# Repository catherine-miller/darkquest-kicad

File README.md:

# darkquest-kicad
KiCad projects for the DarkQuest EMCal readout
Each folder contains a KiCad project called <title>.kicad_pro
The revision number is in the title of each folder.

As of June 2024, the revisions in use are

SiPM motherboard with attenuator: 6.1

SiPM motherboard, no attenuator: 6.2 (use a 0 ohm resistor on resistor pad or a solder blob)

Chip carrier Rev 2.0

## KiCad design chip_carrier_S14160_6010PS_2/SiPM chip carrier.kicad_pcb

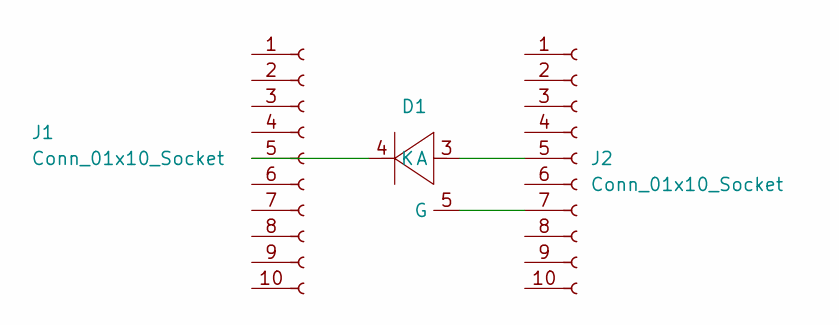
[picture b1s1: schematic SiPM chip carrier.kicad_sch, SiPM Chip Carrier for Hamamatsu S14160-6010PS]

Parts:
D1: S14160_6010PS
J1, J2: Conn_01x10_Socket; PinHeader_1x10_P2.54mm_Vertical

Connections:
unnamed: D1.3 (A), J2.5
unnamed: D1.5 (G), J2.7
unnamed: D1.4 (K), J1.5

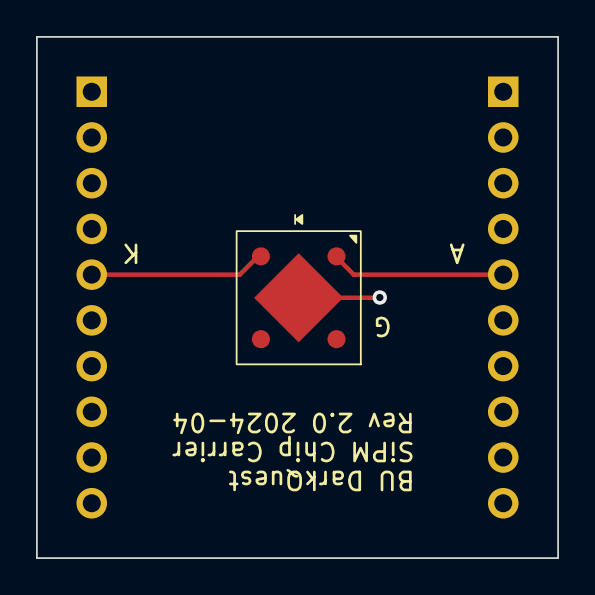
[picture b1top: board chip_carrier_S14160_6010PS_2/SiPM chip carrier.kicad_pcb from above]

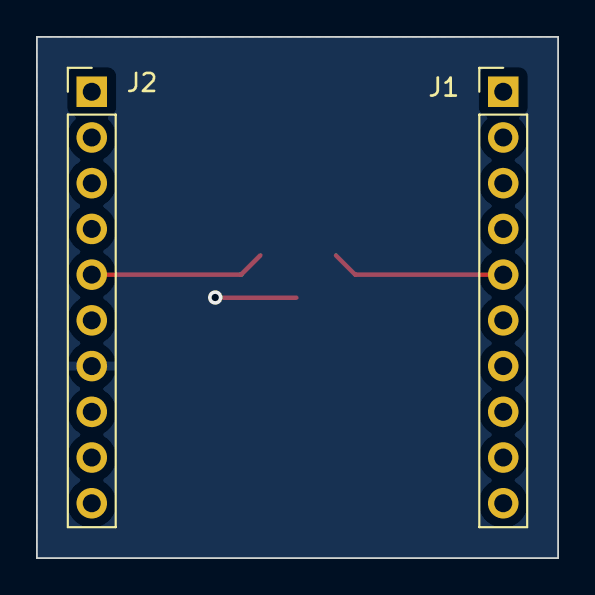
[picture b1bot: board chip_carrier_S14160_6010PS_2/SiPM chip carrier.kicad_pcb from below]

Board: 2 copper layers, 29.0 x 29.0 mm, 3 parts (2 on the bottom side), 3 nets.

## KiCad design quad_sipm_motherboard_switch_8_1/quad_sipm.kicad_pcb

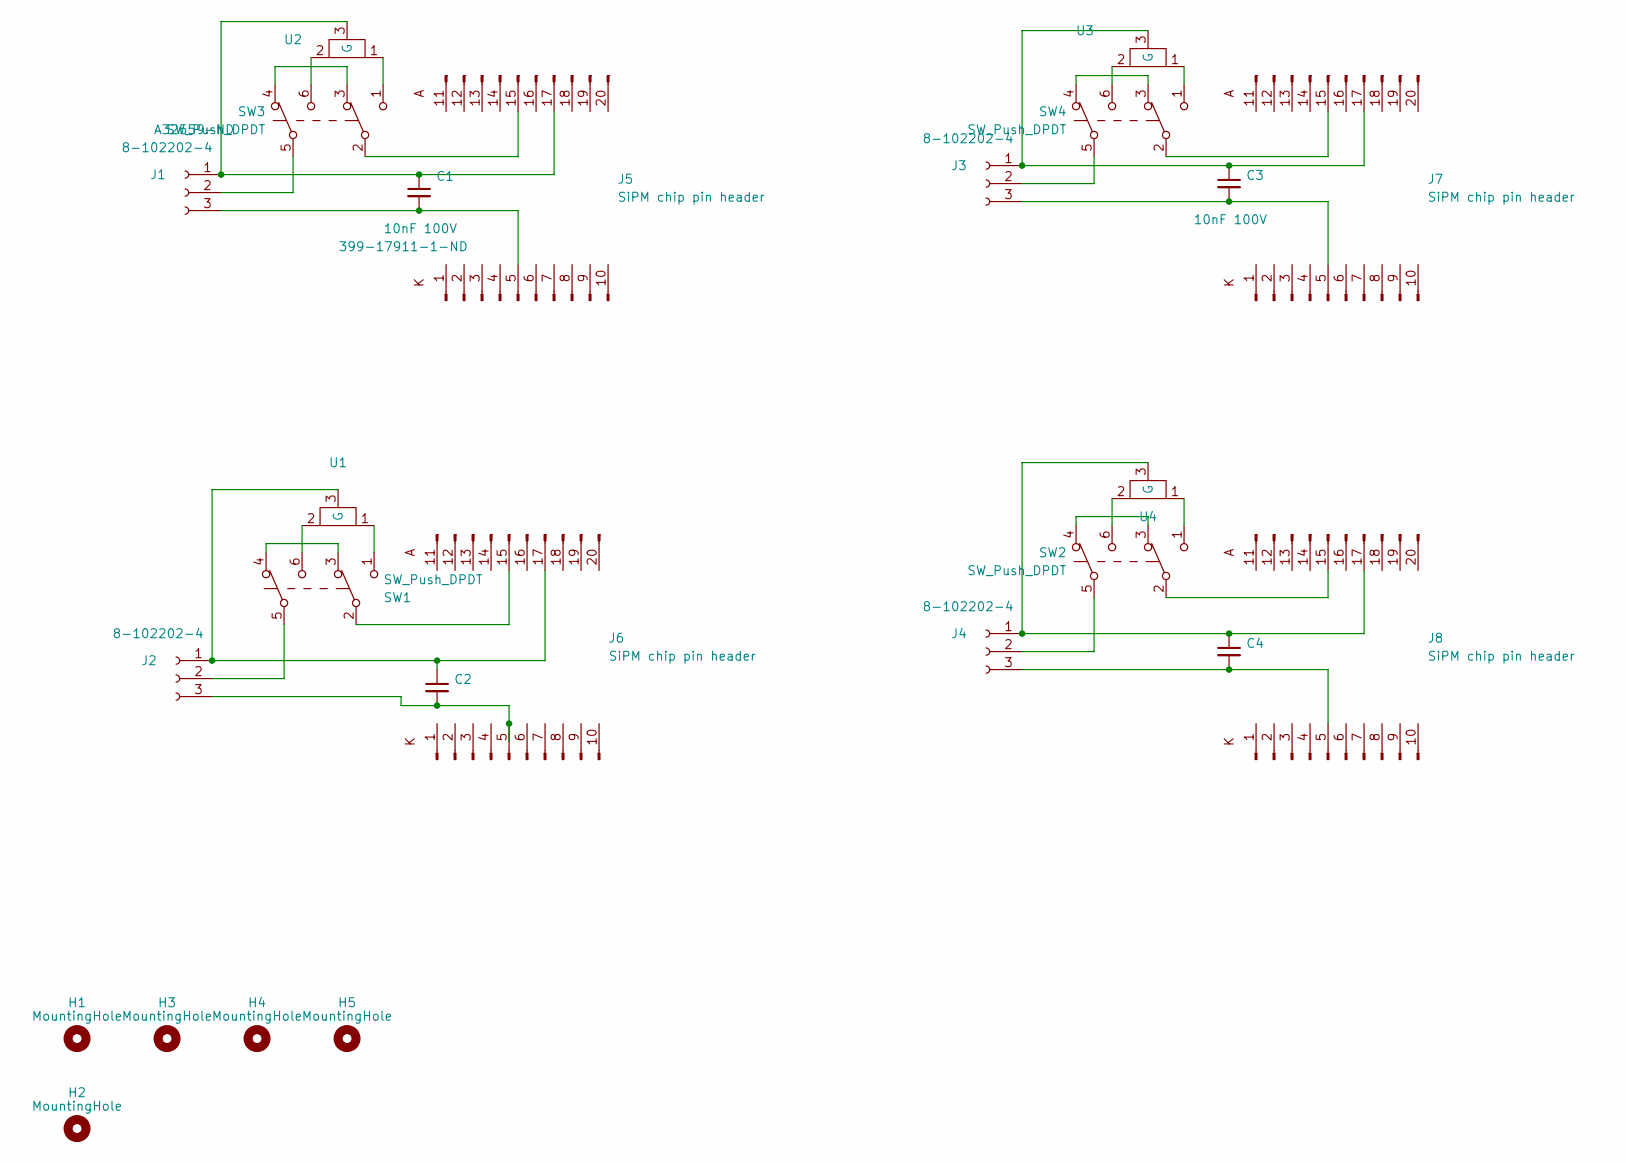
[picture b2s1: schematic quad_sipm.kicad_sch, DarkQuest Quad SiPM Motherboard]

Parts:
C1, C2, C3, C4: 10nF 100V; C_1206_3216Metric_Pad1.33x1.80mm_HandSolder; DigiKey 399-17911-1-ND
H1, H3, H4, H5: MountingHole; MountingHole_6.4_pad
H2: MountingHole; MountingHole_8.4mm_M8_Pad
J1, J2, J3, J4: 8-102202-4; PinHeader_1x03_P2.54mm_Vertical; DigiKey A32559-ND
J5, J6, J7, J8: SiPM chip pin header; chip_carrier_pin_header
SW1, SW2, SW3, SW4: SW_Push_DPDT; Nidec_DPDT_CS422YTA
U1, U2, U3, U4: D10AA20Z4

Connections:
unnamed: C1.1, J1.1, J5.17 (Pin_7), U2.3 (G)
unnamed: J1.2, SW3.5 (B)
unnamed: C1.2, J1.3, J5.5
unnamed: C2.1, J2.1, J6.17 (Pin_7), U1.3 (G)
unnamed: J2.2, SW1.5 (B)
unnamed: C2.2, J2.3, J6.5
unnamed: C3.1, J3.1, J7.17 (Pin_7), U3.3 (G)
unnamed: J3.2, SW4.5 (B)
unnamed: C3.2, J3.3, J7.5
unnamed: C4.1, J4.1, J8.17 (Pin_7), U4.3 (G)
unnamed: J4.2, SW2.5 (B)
unnamed: C4.2, J4.3, J8.5
unnamed: J5.15 (Pin_5), SW3.2
unnamed: J6.15 (Pin_5), SW1.2
unnamed: J7.15 (Pin_5), SW4.2
unnamed: J8.15 (Pin_5), SW2.2
unnamed: SW1.6 (0), U1.2
unnamed: SW1.3 (A), SW1.4 (A)
unnamed: SW1.1 (C), U1.1
unnamed: SW2.6 (0), U4.2
unnamed: SW2.3 (A), SW2.4 (A)
unnamed: SW2.1 (C), U4.1
unnamed: SW3.6 (0), U2.2
unnamed: SW3.3 (A), SW3.4 (A)
unnamed: SW3.1 (C), U2.1
unnamed: SW4.6 (0), U3.2
unnamed: SW4.3 (A), SW4.4 (A)
unnamed: SW4.1 (C), U3.1

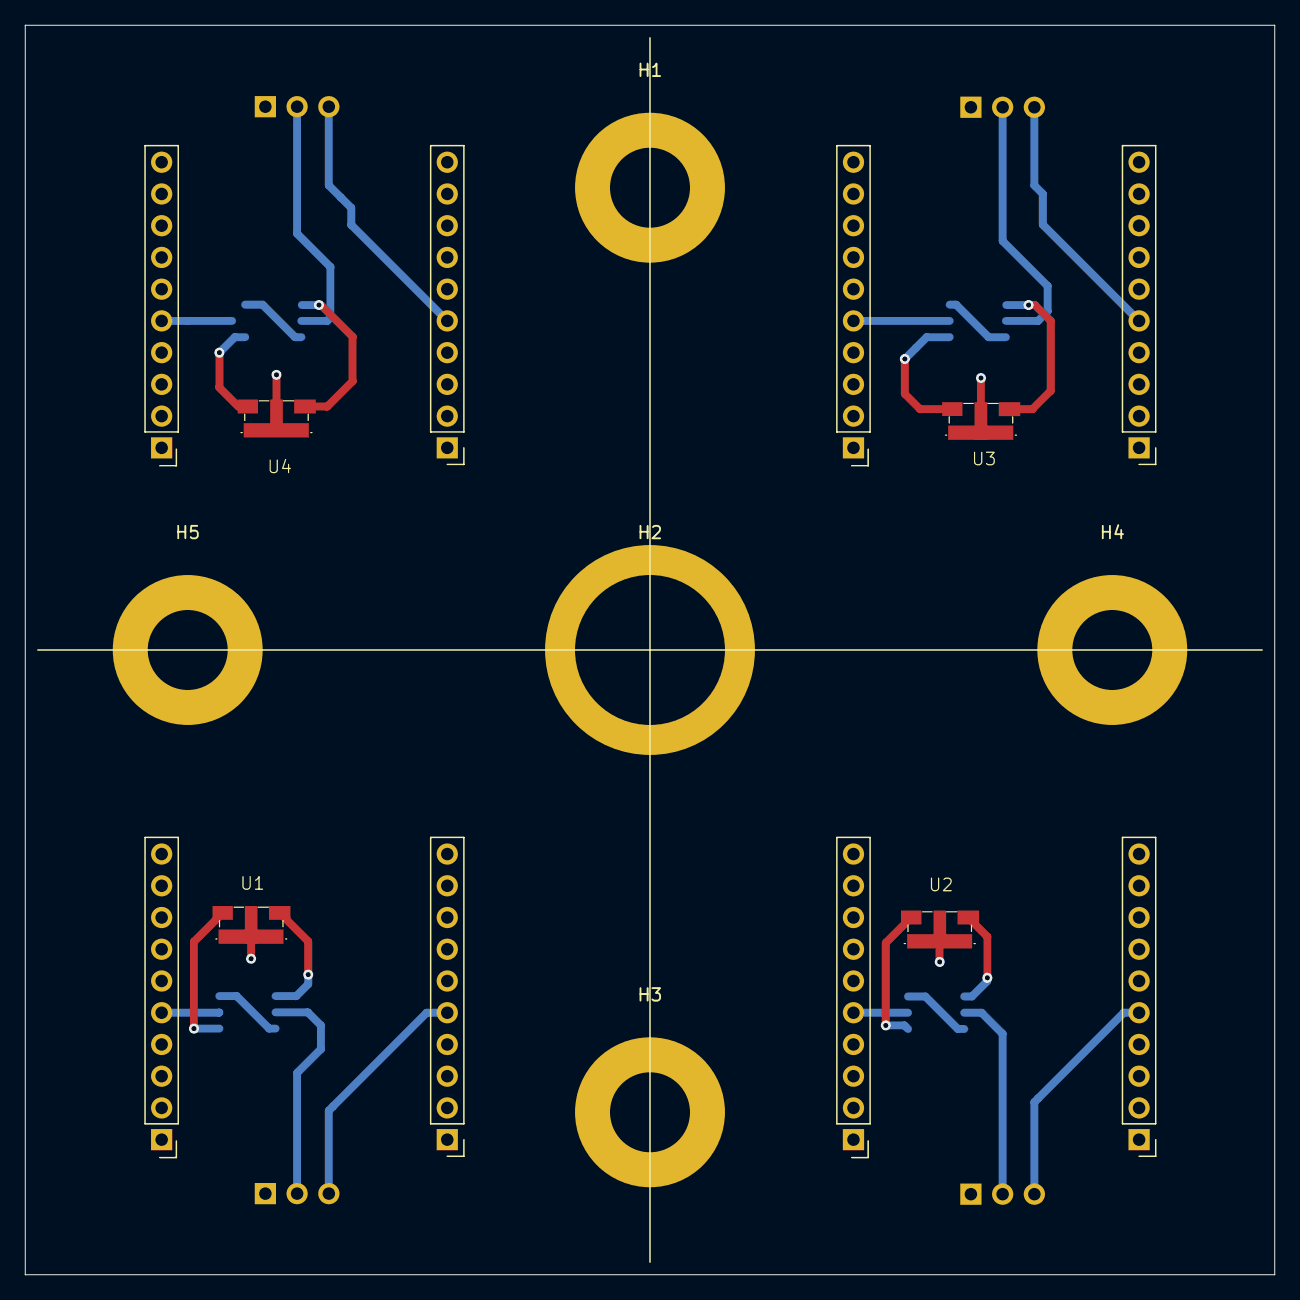
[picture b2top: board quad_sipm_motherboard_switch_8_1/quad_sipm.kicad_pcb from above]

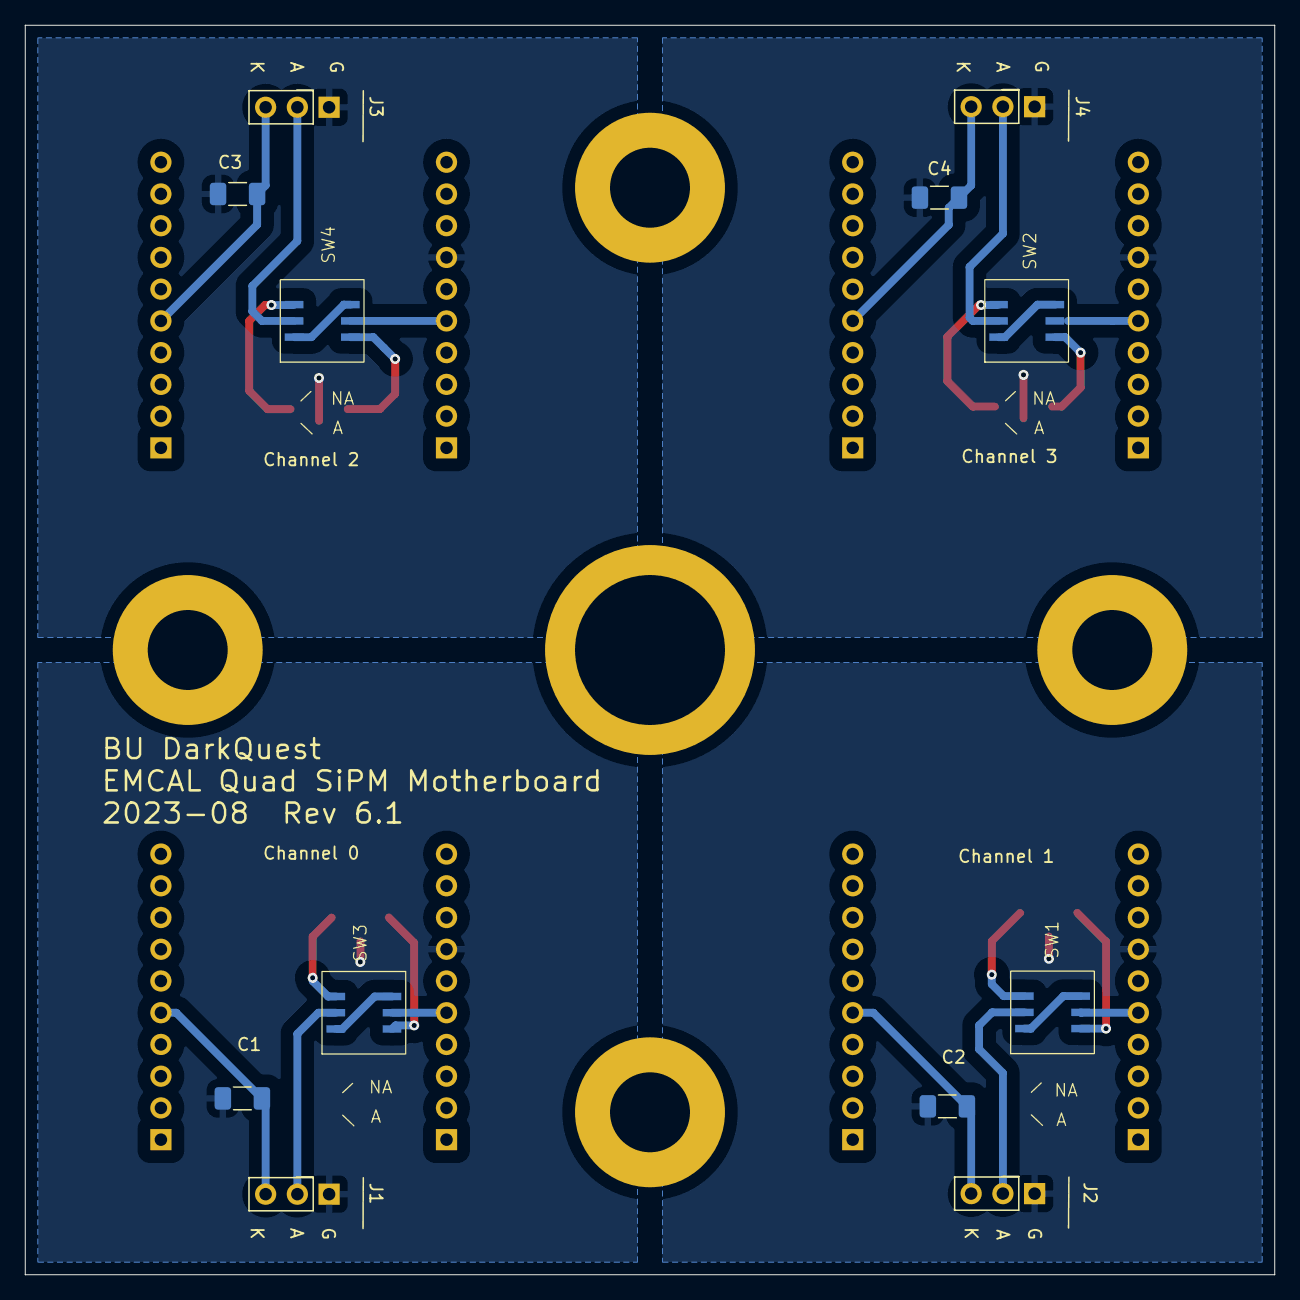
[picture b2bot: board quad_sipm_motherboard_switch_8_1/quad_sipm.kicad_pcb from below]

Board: 2 copper layers, 100.0 x 100.0 mm, 25 parts (12 on the bottom side), 28 nets.

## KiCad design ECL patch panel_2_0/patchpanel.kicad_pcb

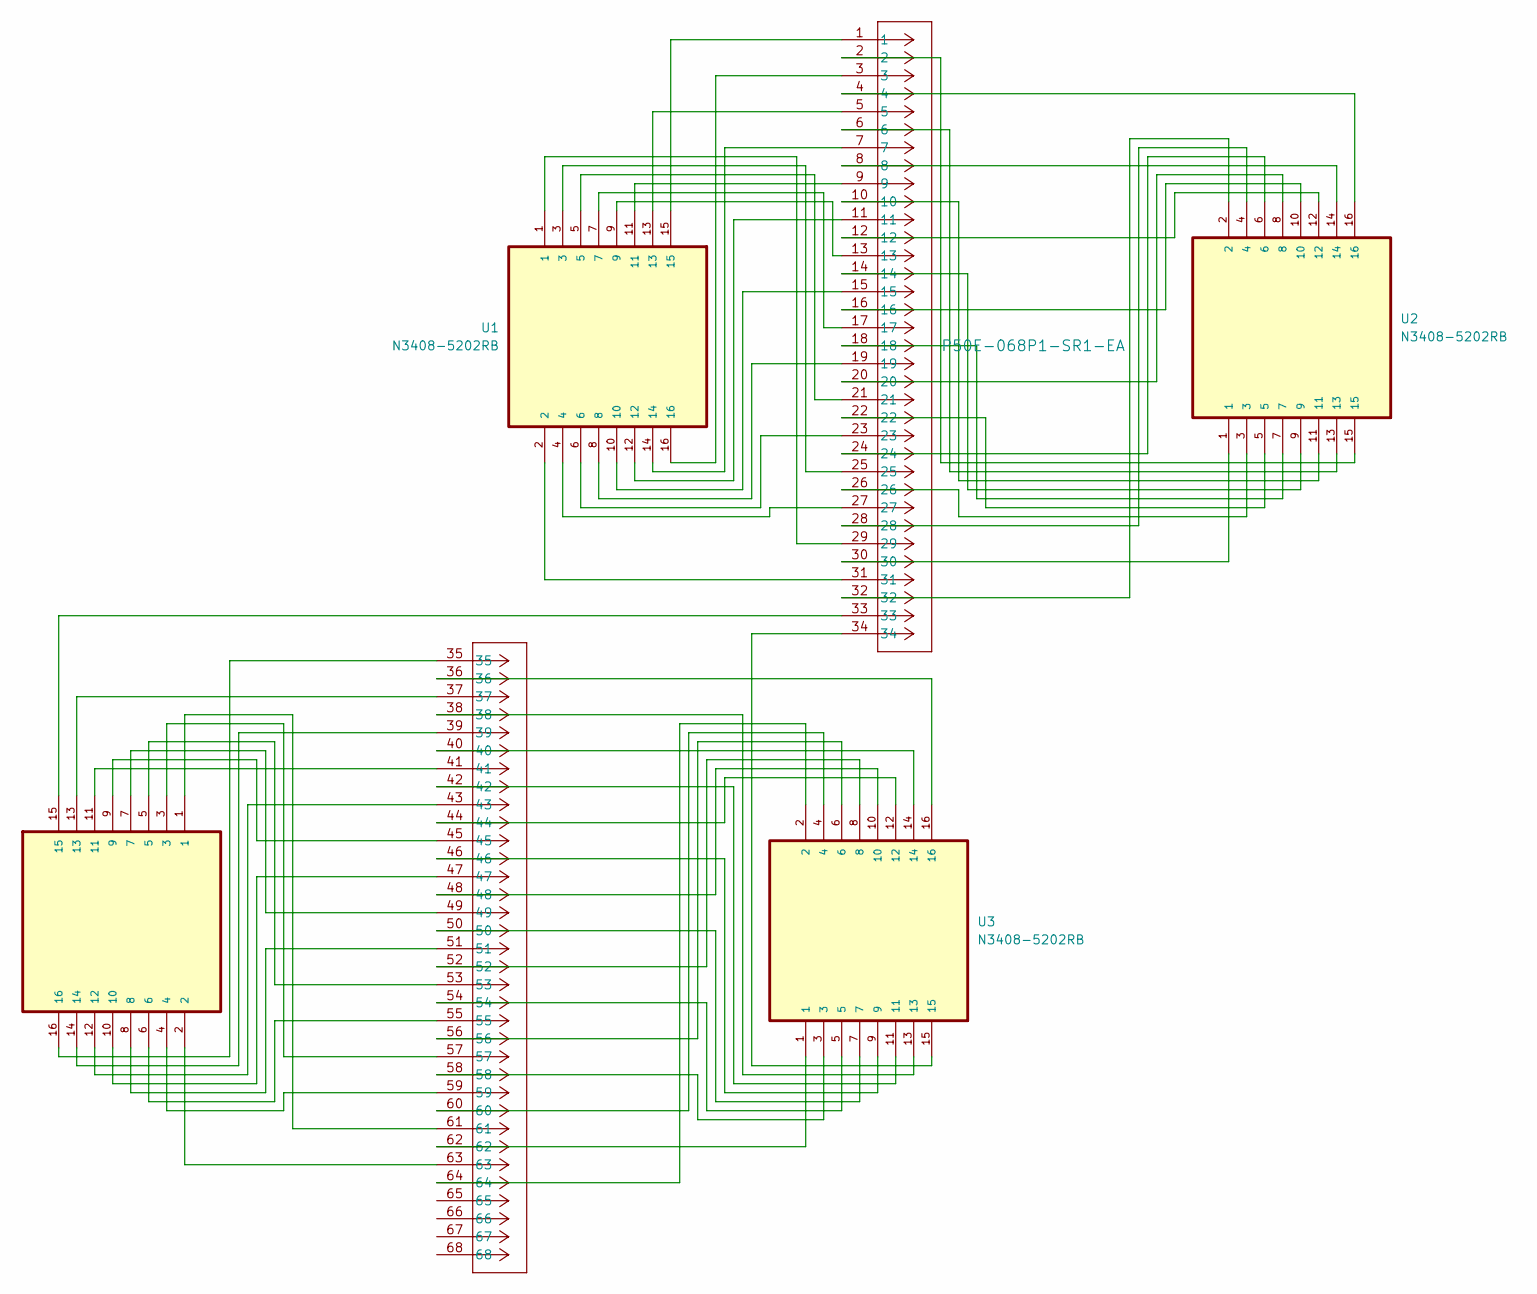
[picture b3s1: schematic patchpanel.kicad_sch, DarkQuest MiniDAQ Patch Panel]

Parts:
J1: P50E-068P1-SR1-EA; CONN_P50E-068P1-SR1-EA_3MM
U1, U2, U3, U4: N3408-5202RB; 3M_N3408-5202RB; MPN N3408-5202RB

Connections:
unnamed: J1.1, U1.15
unnamed: J1.2, U2.15
unnamed: J1.3, U1.16
unnamed: J1.4, U2.16
unnamed: J1.5, U1.13
unnamed: J1.6, U2.13
unnamed: J1.7, U1.14
unnamed: J1.8, U2.14
unnamed: J1.9, U1.11
unnamed: J1.10, U2.11
unnamed: J1.11, U1.12
unnamed: J1.12, U2.12
unnamed: J1.13, U1.9
unnamed: J1.14, U2.9
unnamed: J1.15, U1.10
unnamed: J1.16, U2.10
unnamed: J1.17, U1.7
unnamed: J1.18, U2.7
unnamed: J1.19, U1.8
unnamed: J1.20, U2.8
unnamed: J1.21, U1.5
unnamed: J1.22, U2.5
unnamed: J1.23, U1.6
unnamed: J1.24, U2.6
unnamed: J1.25, U1.3
unnamed: J1.26, U2.3
unnamed: J1.27, U1.4
unnamed: J1.28, U2.4
unnamed: J1.29, U1.1
unnamed: J1.30, U2.1
unnamed: J1.31, U1.2
unnamed: J1.32, U2.2
unnamed: J1.33, U4.15
unnamed: J1.34, U3.15
unnamed: J1.35, U4.16
unnamed: J1.36, U3.16
unnamed: J1.37, U4.13
unnamed: J1.38, U3.13
unnamed: J1.39, U4.14
unnamed: J1.40, U3.14
unnamed: J1.41, U4.11
unnamed: J1.42, U3.11
unnamed: J1.43, U4.12
unnamed: J1.44, U3.12
unnamed: J1.45, U4.9
unnamed: J1.46, U3.9
unnamed: J1.47, U4.10
unnamed: J1.48, U3.10
unnamed: J1.49, U4.7
unnamed: J1.50, U3.7
unnamed: J1.51, U4.8
unnamed: J1.52, U3.8
unnamed: J1.53, U4.5
unnamed: J1.54, U3.5
unnamed: J1.55, U4.6
unnamed: J1.56, U3.6
unnamed: J1.57, U4.3
unnamed: J1.58, U3.3
unnamed: J1.59, U4.4
unnamed: J1.60, U3.4
unnamed: J1.61, U4.1
unnamed: J1.62, U3.1
unnamed: J1.63, U4.2
unnamed: J1.64, U3.2

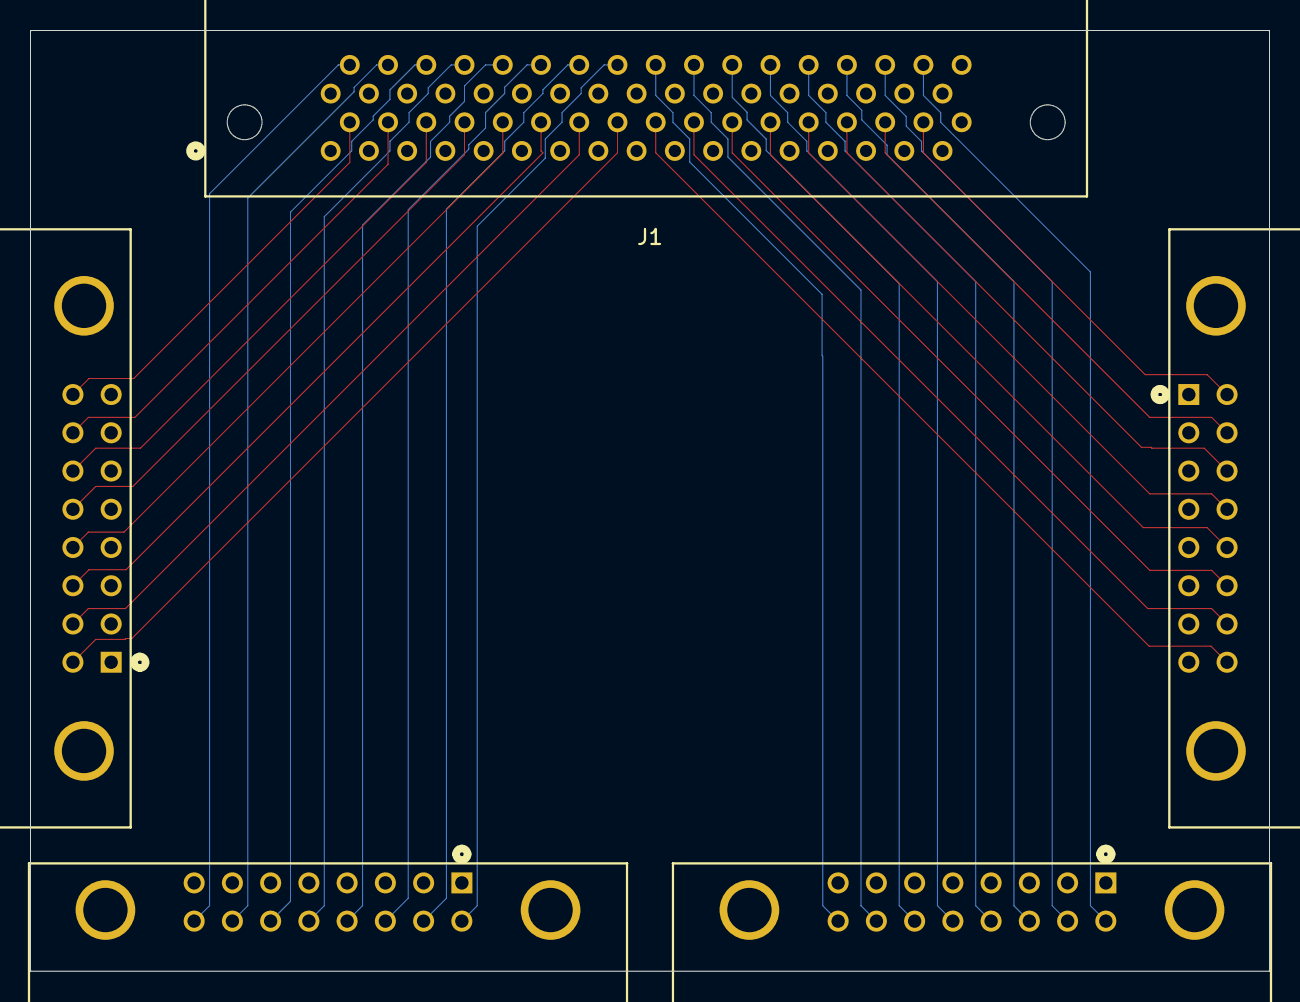
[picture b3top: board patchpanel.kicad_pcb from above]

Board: 4 copper layers, 82.3 x 62.5 mm, 5 parts (0 on the bottom side), 64 nets.

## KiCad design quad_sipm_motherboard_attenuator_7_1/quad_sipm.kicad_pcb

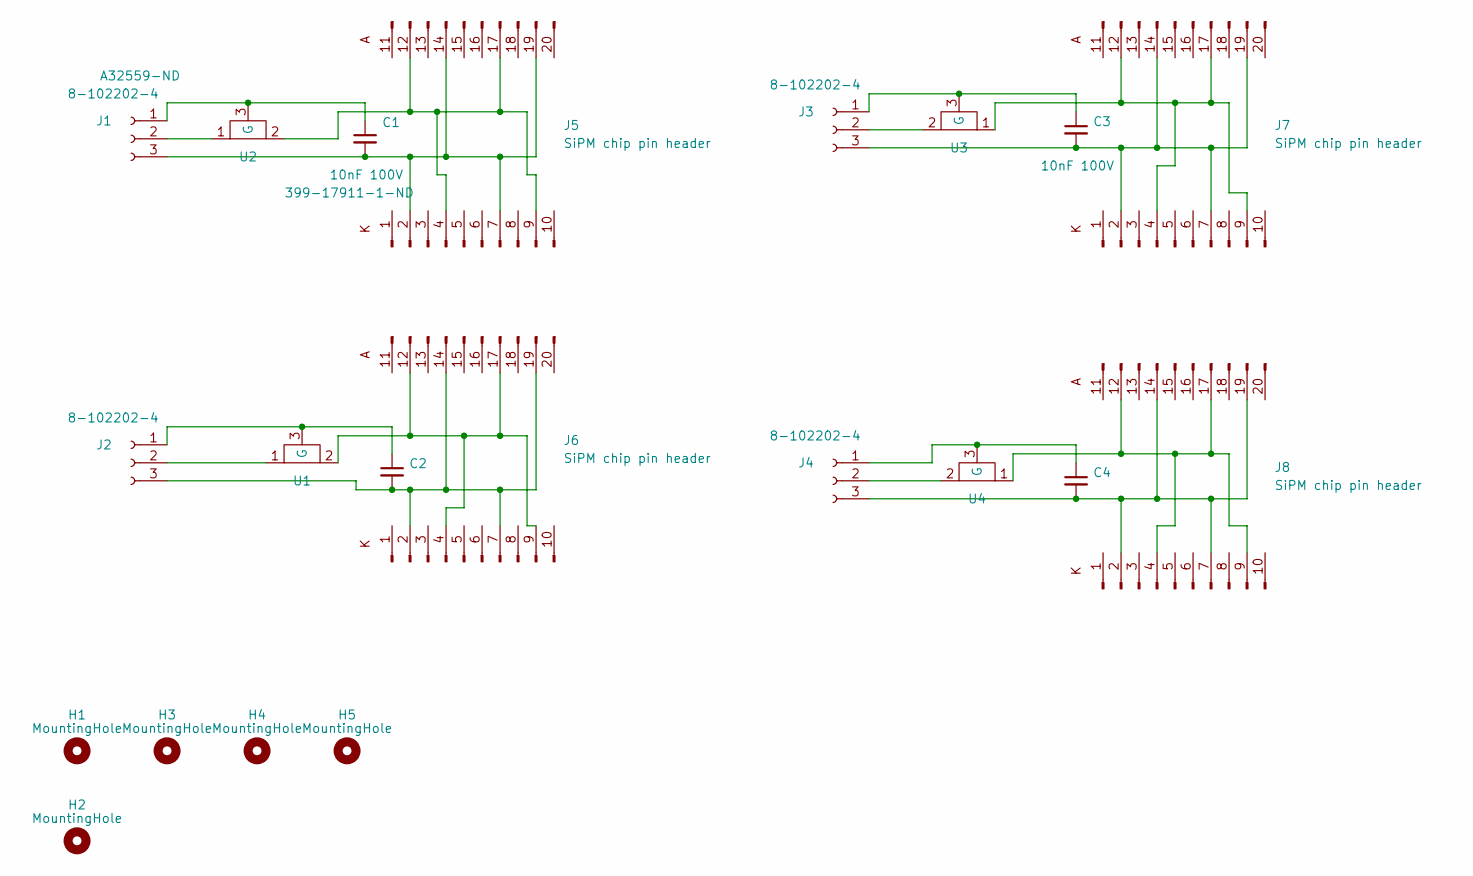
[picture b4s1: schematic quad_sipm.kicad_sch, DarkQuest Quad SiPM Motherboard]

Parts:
C1, C2, C3, C4: 10nF 100V; C_1206_3216Metric_Pad1.33x1.80mm_HandSolder; DigiKey 399-17911-1-ND
H1, H3, H4, H5: MountingHole; MountingHole_6.4_pad
H2: MountingHole; MountingHole_8.4mm_M8_Pad
J1, J2, J3, J4: 8-102202-4; PinHeader_1x03_P2.54mm_Vertical; DigiKey A32559-ND
J5, J6, J7, J8: SiPM chip pin header; chip_carrier_pin_header
U1, U2, U3, U4: D10AA20Z4

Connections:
unnamed: C1.1, J1.1, U2.3 (G)
unnamed: J1.2, U2.1
unnamed: C1.2, J1.3, J5.2, J5.7, J5.14 (Pin_4), J5.19 (Pin_9)
unnamed: C2.1, J2.1, U1.3 (G)
unnamed: J2.2, U1.1
unnamed: C2.2, J2.3, J6.2, J6.7, J6.14 (Pin_4), J6.19 (Pin_9)
unnamed: C3.1, J3.1, U3.3 (G)
unnamed: J3.2, U3.2
unnamed: C3.2, J3.3, J7.2, J7.7, J7.14 (Pin_4), J7.19 (Pin_9)
unnamed: C4.1, J4.1, U4.3 (G)
unnamed: J4.2, U4.2
unnamed: C4.2, J4.3, J8.2, J8.7, J8.14 (Pin_4), J8.19 (Pin_9)
unnamed: J5.4, J5.9, J5.12 (Pin_2), J5.17 (Pin_7), U2.2
unnamed: J6.4, J6.9, J6.12 (Pin_2), J6.17 (Pin_7), U1.2
unnamed: J7.4, J7.9, J7.12 (Pin_2), J7.17 (Pin_7), U3.1
unnamed: J8.4, J8.9, J8.12 (Pin_2), J8.17 (Pin_7), U4.1

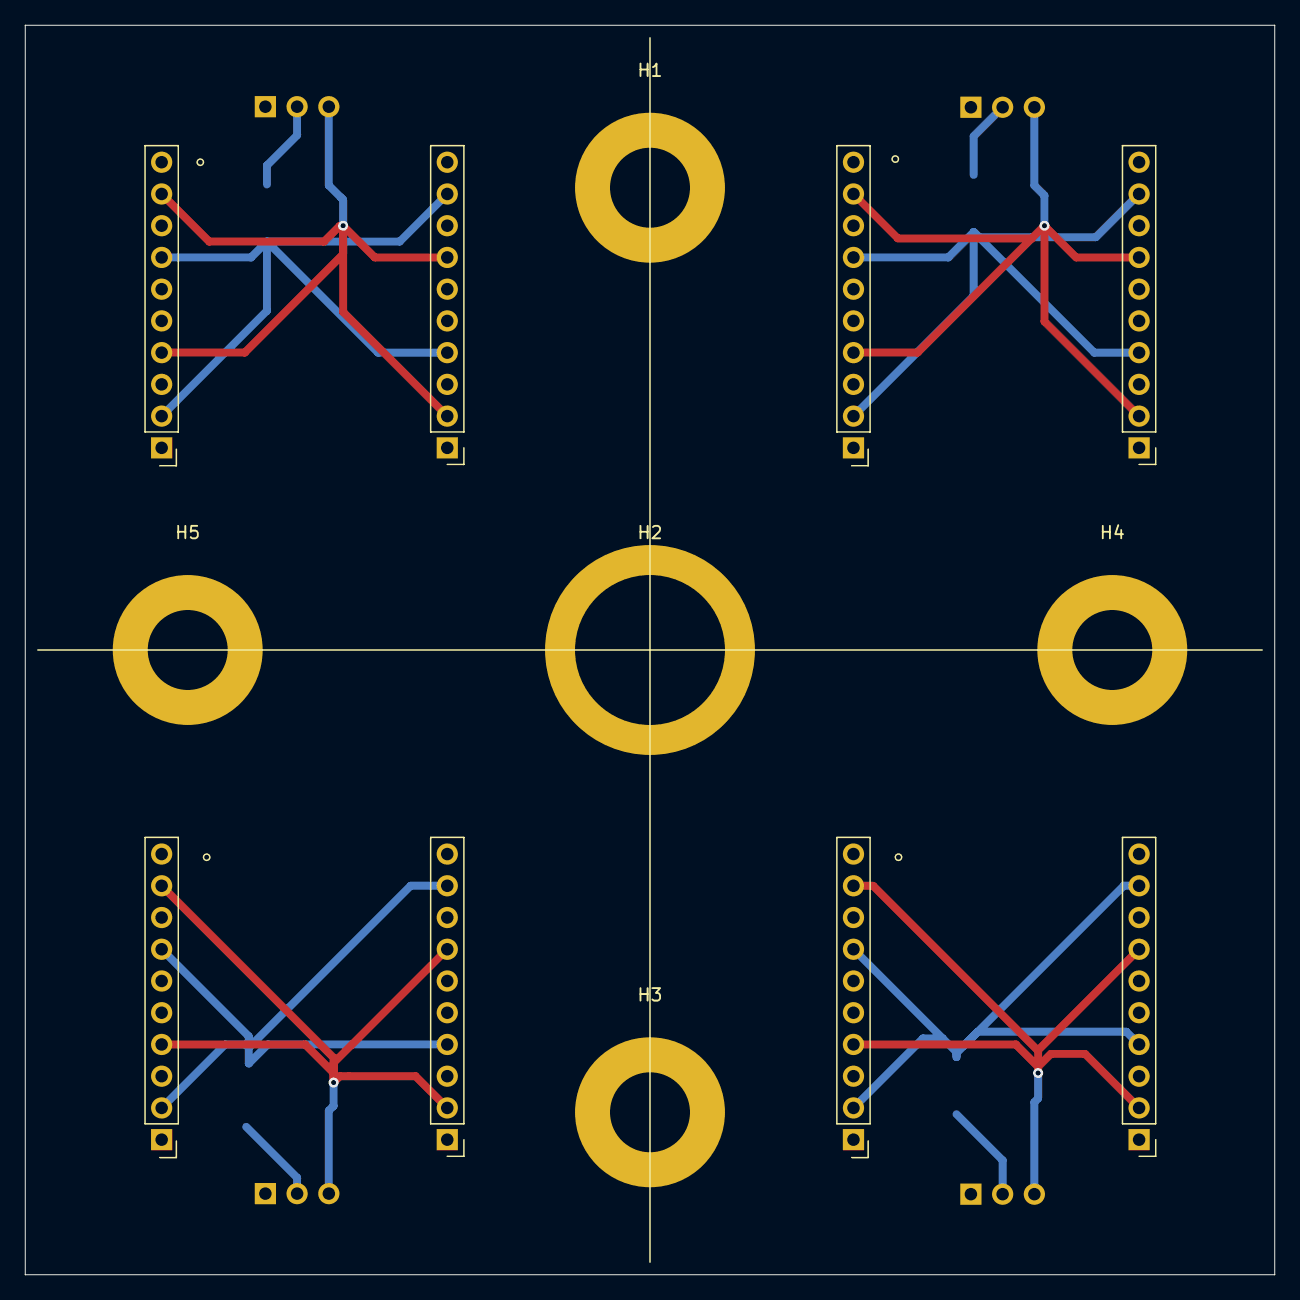
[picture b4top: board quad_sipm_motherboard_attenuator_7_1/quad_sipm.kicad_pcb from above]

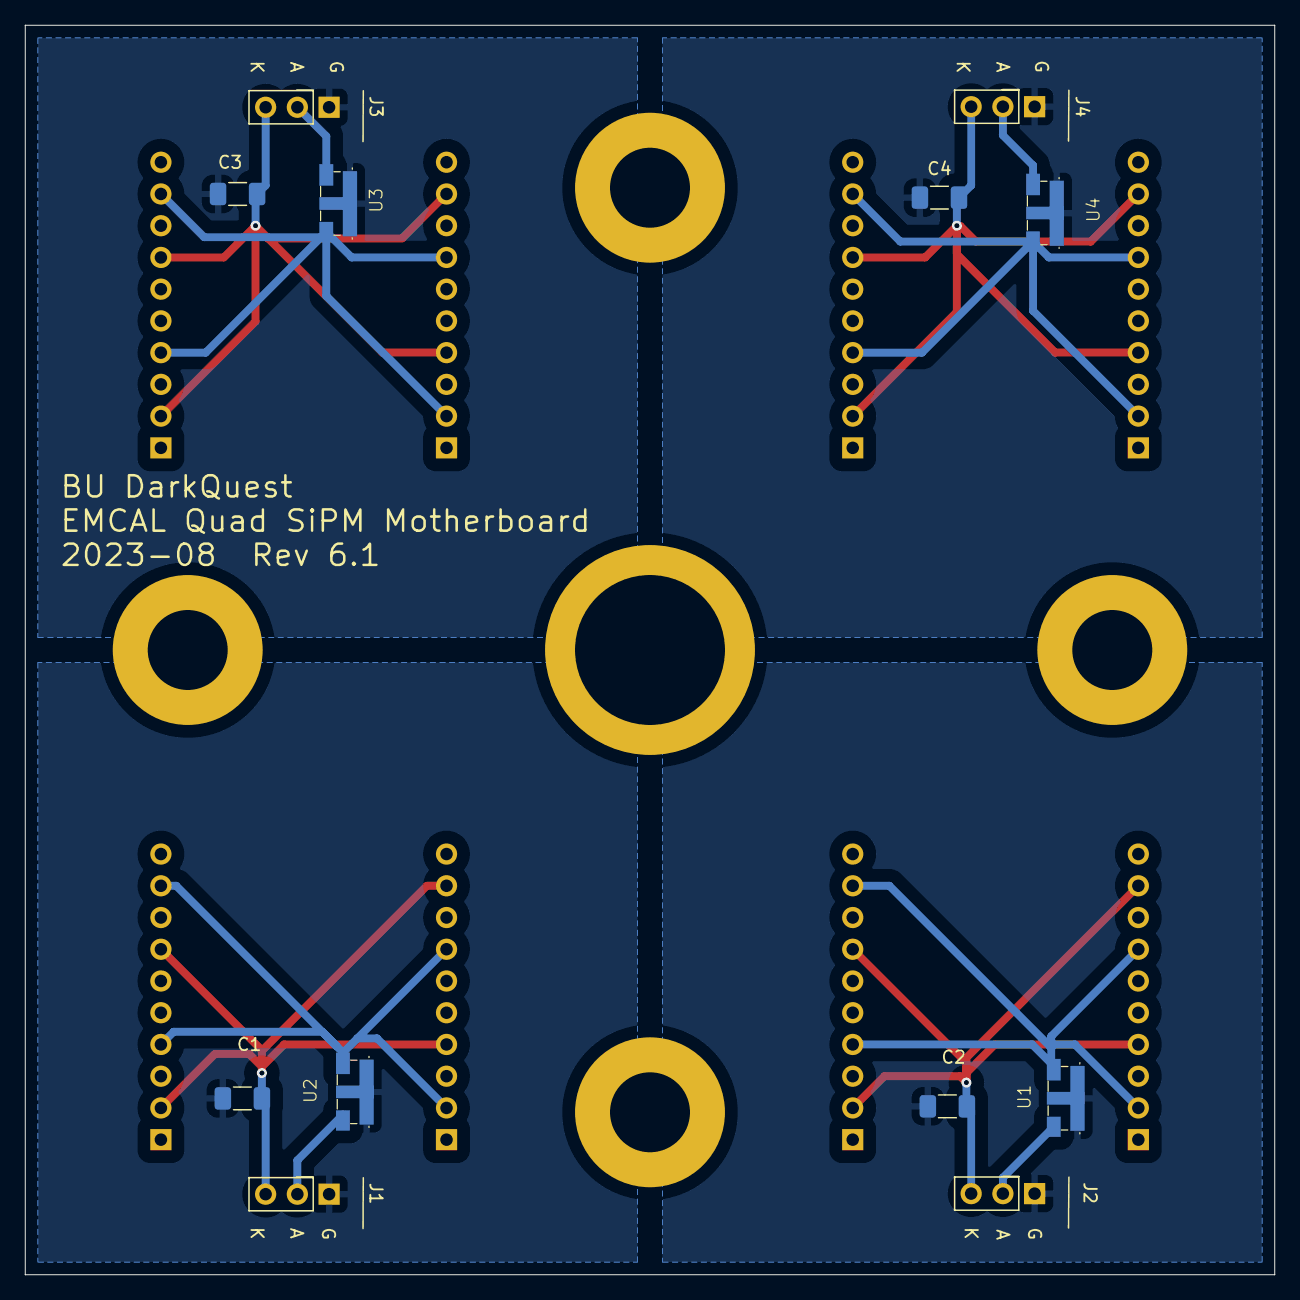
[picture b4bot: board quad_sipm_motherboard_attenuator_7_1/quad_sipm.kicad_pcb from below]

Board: 2 copper layers, 100.0 x 100.0 mm, 21 parts (12 on the bottom side), 16 nets.

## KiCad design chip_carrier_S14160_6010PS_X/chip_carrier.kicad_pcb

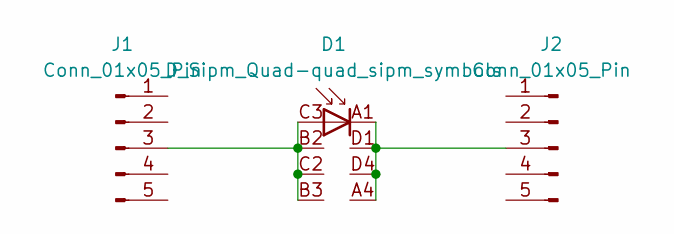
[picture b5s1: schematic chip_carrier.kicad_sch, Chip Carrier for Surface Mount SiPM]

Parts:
D1: D_Sipm_Quad-quad_sipm_symbols; sipm_6x6_bga_SMD
J1, J2: Conn_01x05_Pin; Header_connector

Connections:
unnamed: D1.B2 (A), D1.B3 (A), D1.C2 (A), D1.C3 (A), J1.3
unnamed: D1.A1 (K), D1.A4 (K), D1.D1 (K), D1.D4 (K), J2.3

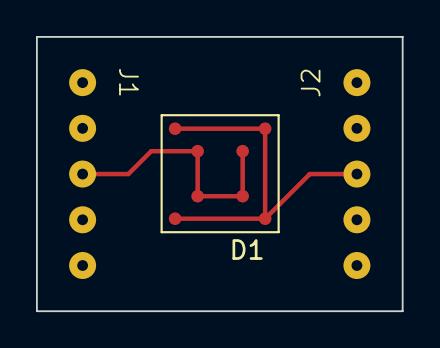
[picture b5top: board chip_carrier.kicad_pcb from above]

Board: 2 copper layers, 20.3 x 15.2 mm, 3 parts (0 on the bottom side), 2 nets.

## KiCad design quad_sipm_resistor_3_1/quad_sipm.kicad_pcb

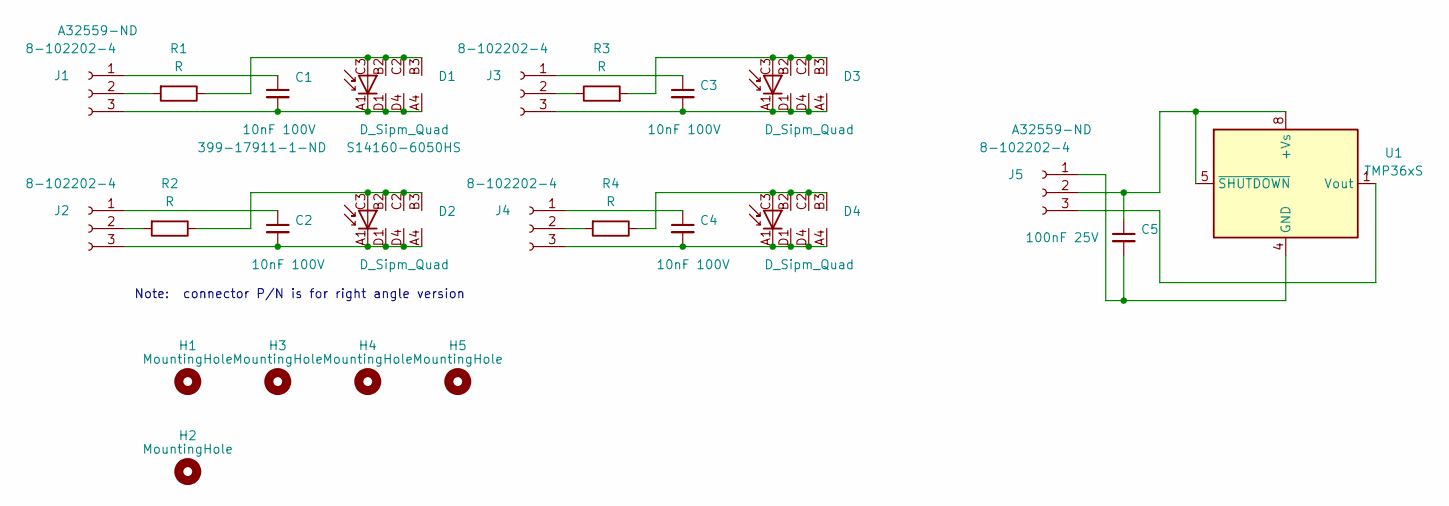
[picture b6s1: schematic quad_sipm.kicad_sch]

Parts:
C1, C2, C3, C4: 10nF 100V; C_1206_3216Metric_Pad1.33x1.80mm_HandSolder; DigiKey 399-17911-1-ND
C5: 100nF 25V; C_1206_3216Metric_Pad1.33x1.80mm_HandSolder; DigiKey 399-C1206C104F3GECAUTOCT-ND
D1, D2, D3, D4: D_Sipm_Quad; sipm_6x6_bga_SMD
H1, H3, H4, H5: MountingHole; MountingHole_6.4_pad
H2: MountingHole; MountingHole_8.4mm_M8_Pad
J1, J2, J3, J4, J5: 8-102202-4; PinHeader_1x03_P2.54mm_Vertical; DigiKey A32559-ND
R1, R2, R3, R4: R; 1206_VIS-L
U1: TMP36xS; SOIC-8_3.9x4.9mm_P1.27mm

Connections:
unnamed: D1.B2 (A), D1.B3 (A), D1.C2 (A), D1.C3 (A), R1.1
unnamed: D2.B2 (A), D2.B3 (A), D2.C2 (A), D2.C3 (A), R2.1
unnamed: D3.B2 (A), D3.B3 (A), D3.C2 (A), D3.C3 (A), R3.2
unnamed: D4.B2 (A), D4.B3 (A), D4.C2 (A), D4.C3 (A), R4.1
unnamed: C1.1, J1.1
unnamed: J1.2, R1.2
unnamed: C1.2, D1.A1 (K), D1.A4 (K), D1.D1 (K), D1.D4 (K), J1.3
unnamed: C2.1, J2.1
unnamed: J2.2, R2.2
unnamed: C2.2, D2.A1 (K), D2.A4 (K), D2.D1 (K), D2.D4 (K), J2.3
unnamed: C3.1, J3.1
unnamed: J3.2, R3.1
unnamed: C3.2, D3.A1 (K), D3.A4 (K), D3.D1 (K), D3.D4 (K), J3.3
unnamed: C4.1, J4.1
unnamed: J4.2, R4.2
unnamed: C4.2, D4.A1 (K), D4.A4 (K), D4.D1 (K), D4.D4 (K), J4.3
unnamed: C5.2, J5.1, U1.4 (GND)
unnamed: C5.1, J5.2, U1.5 (~SHUTDOWN), U1.8 (+Vs)
unnamed: J5.3, U1.1 (Vout)

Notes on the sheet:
Note: connector P/N is for right angle version

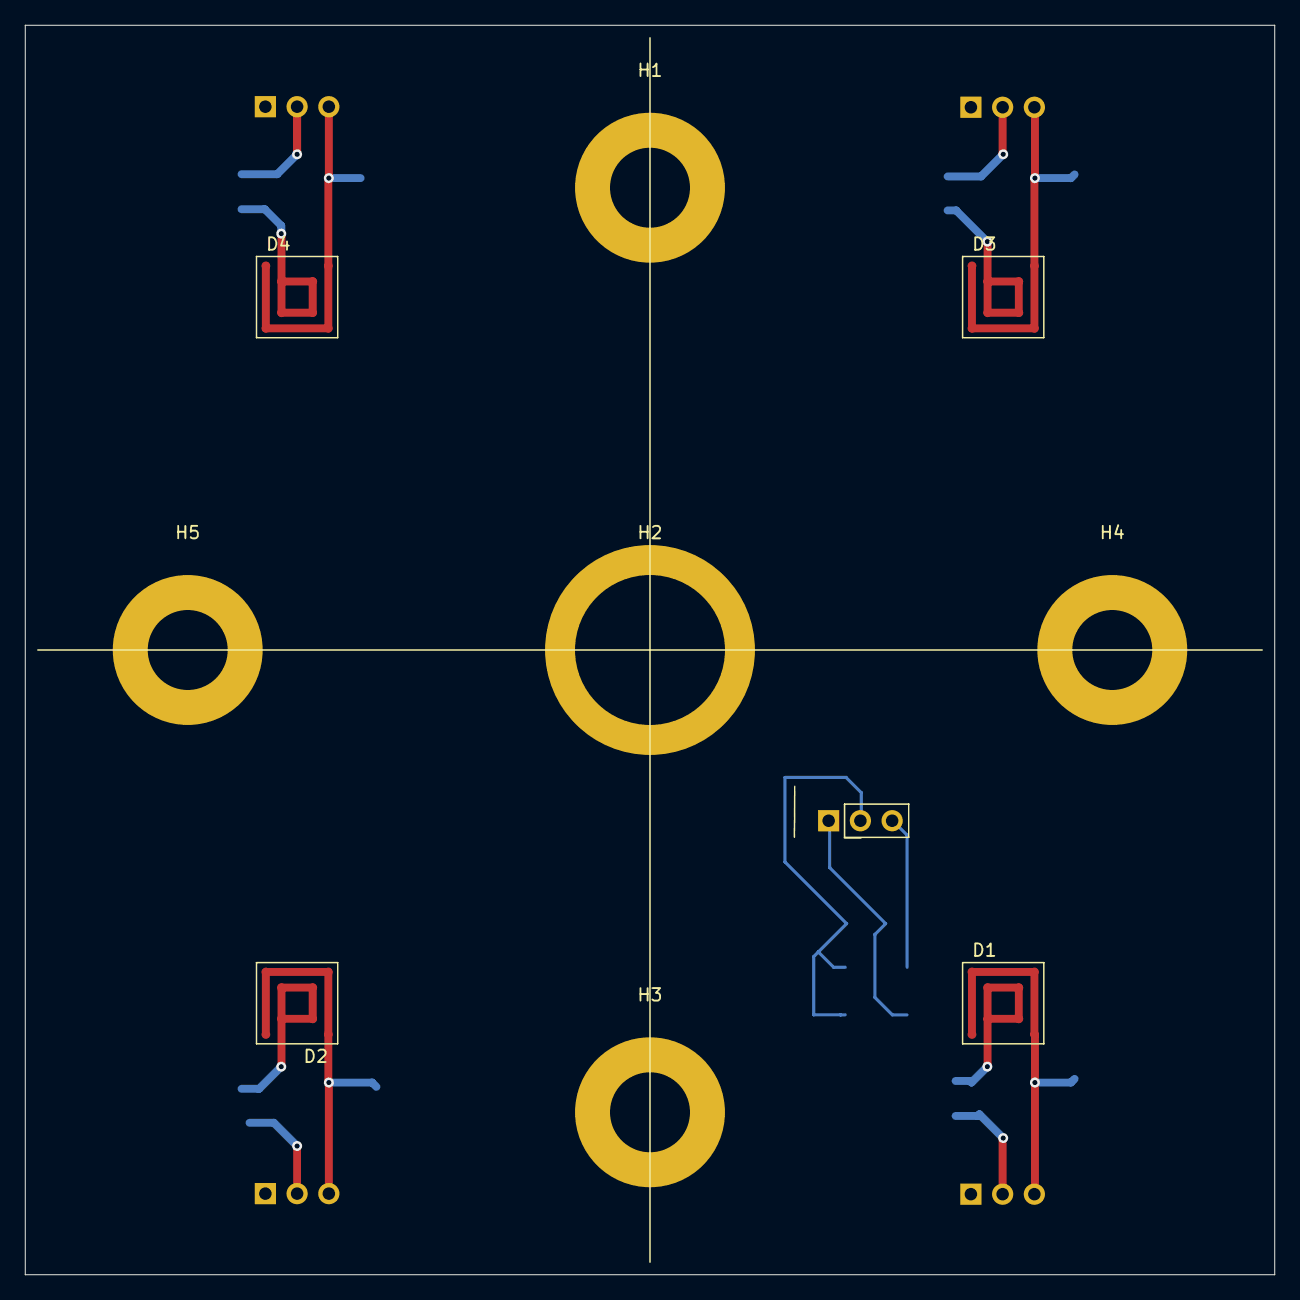
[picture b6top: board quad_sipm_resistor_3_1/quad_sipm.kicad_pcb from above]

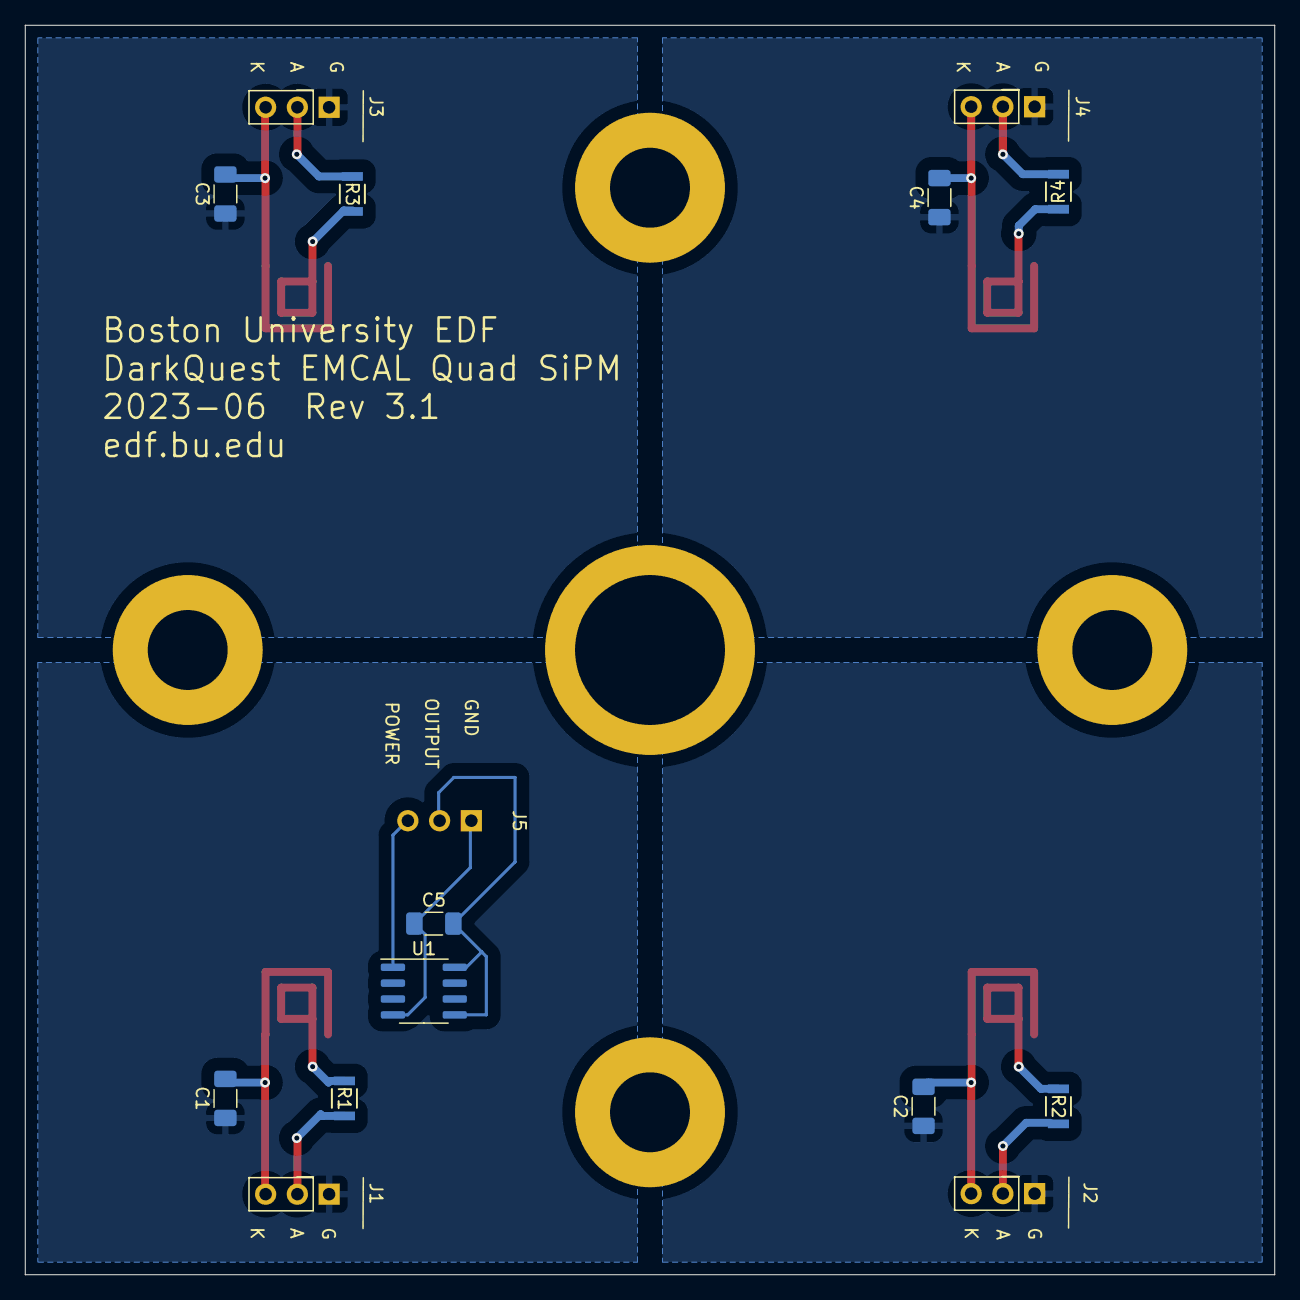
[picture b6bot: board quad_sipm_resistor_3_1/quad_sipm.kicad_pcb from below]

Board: 2 copper layers, 100.0 x 100.0 mm, 24 parts (14 on the bottom side), 19 nets.
